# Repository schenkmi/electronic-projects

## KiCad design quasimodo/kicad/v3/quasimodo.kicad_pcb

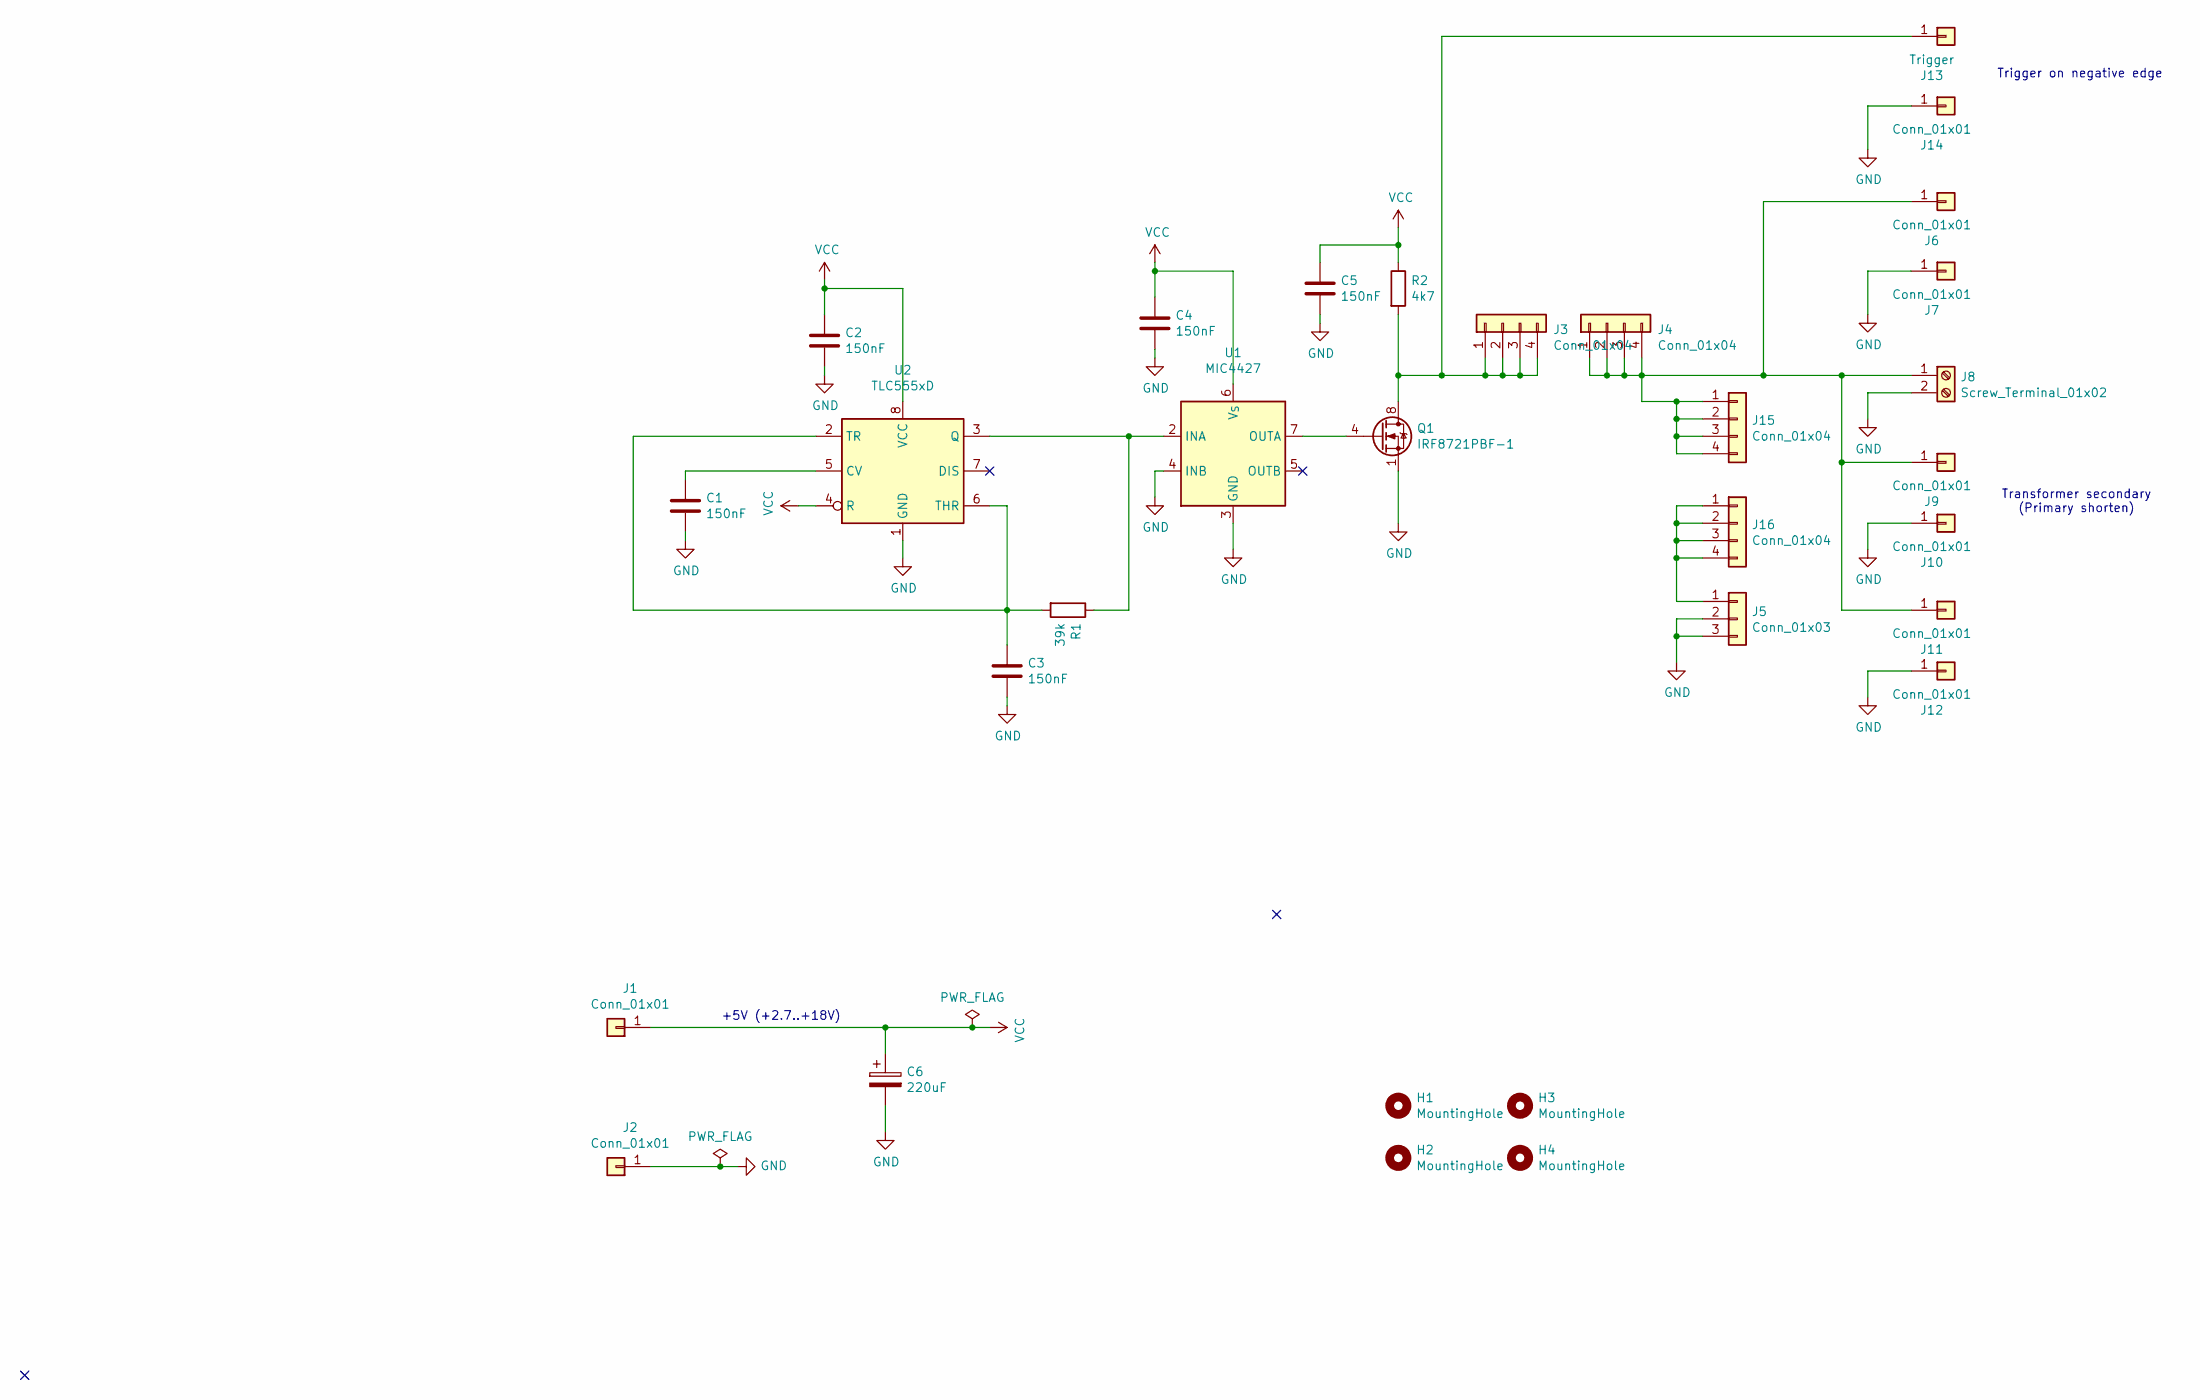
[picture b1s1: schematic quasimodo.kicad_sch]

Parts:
C1, C2, C3, C4, C5: 150nF; C_0805_2012Metric_Pad1.18x1.45mm_HandSolder
C6: 220uF; CP_Radial_D8.0mm_P3.50mm
H1, H2, H3, H4: MountingHole; MountingHole_3.2mm_M3
J1, J2, J6, J7, J9, J10, J14: Conn_01x01; Pin_D1.0mm_L10.0mm
J3, J4, J15, J16: Conn_01x04; PinSocket_1x04_P2.54mm_Vertical
J5: Conn_01x03; PinHeader_1x03_P2.54mm_Vertical
J8: Screw_Terminal_01x02; TerminalBlock_RND_205-00012_1x02_P5.00mm_Horizontal
J11, J12: Conn_01x01; Pin_D1.3mm_L11.0mm
J13: Trigger; Pin_D1.0mm_L10.0mm
Q1: IRF8721PBF-1; SOIC-8_3.9x4.9mm_P1.27mm
R1: 39k; R_0805_2012Metric_Pad1.20x1.40mm_HandSolder
R2: 4k7; R_0805_2012Metric_Pad1.20x1.40mm_HandSolder
U1: MIC4427; SOIC-8_3.9x4.9mm_P1.27mm
U2: TLC555xD; SOIC-8_3.9x4.9mm_P1.27mm

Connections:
GND: C1.2, C2.2, C3.2, C4.2, C5.2, C6.2, J2.1, J5.2, J5.3, J7.1, J8.2, J10.1, J12.1, J14.1, Q1.1 (S), Q1.2 (S), Q1.3 (S), U1.3 (GND), U1.4 (INB), U2.1 (GND)
unnamed: C1.1, U2.5 (CV)
unnamed: C3.1, R1.2, U2.2 (TR), U2.6 (THR)
unnamed: J4.1, J4.2, J4.3, J4.4, J6.1, J8.1, J9.1, J11.1, J15.1, J15.2, J15.3, J15.4
unnamed: J3.1, J3.2, J3.3, J3.4, J13.1, Q1.5 (D), Q1.6 (D), Q1.7 (D), Q1.8 (D), R2.2
unnamed: J5.1, J16.1, J16.2, J16.3, J16.4
unnamed: Q1.4 (G), U1.7 (OUTA)
unnamed: R1.1, U1.2 (INA), U2.3 (Q)
VCC: C2.1, C4.1, C5.1, C6.1, J1.1, R2.1, U1.6 (V_{S}), U2.4 (R), U2.8 (VCC)

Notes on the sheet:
+5V (+2.7..+18V)
Transformer secondary (Primary shorten)
Trigger on negative edge

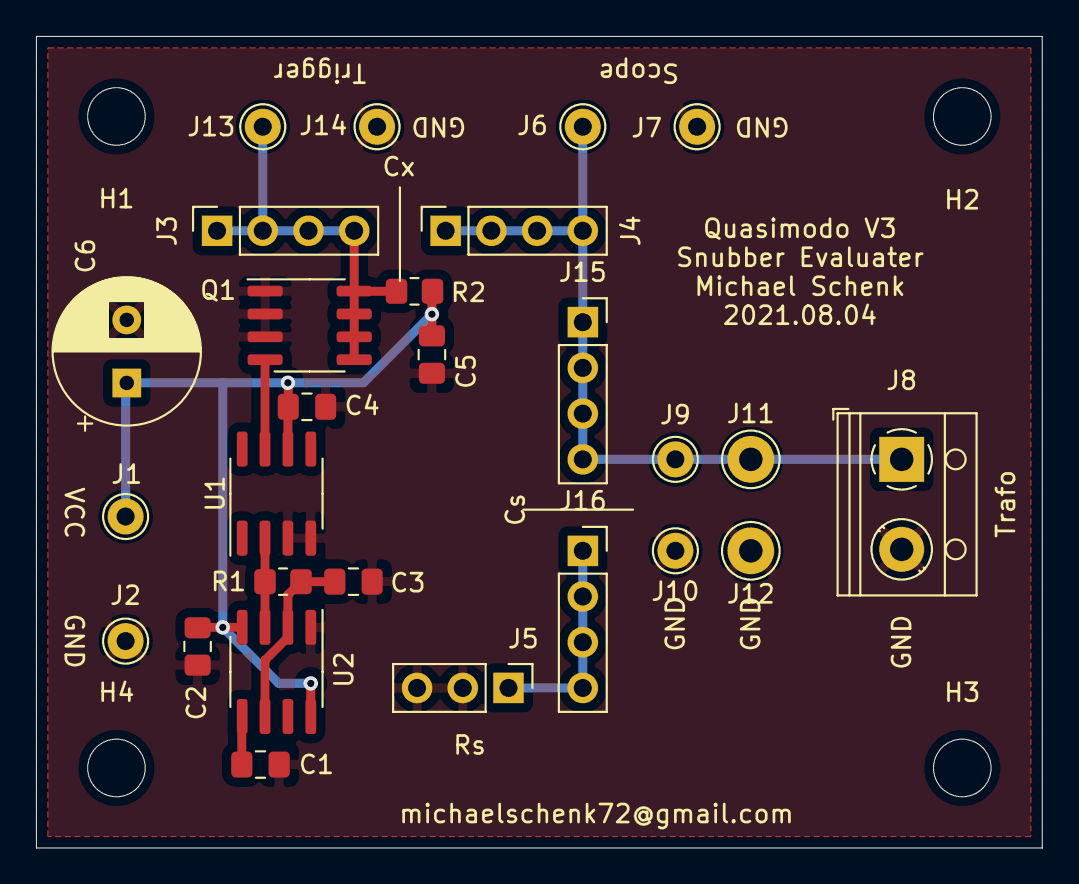
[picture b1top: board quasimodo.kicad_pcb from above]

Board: 2 copper layers, 55.9 x 45.1 mm, 31 parts (0 on the bottom side), 9 nets.

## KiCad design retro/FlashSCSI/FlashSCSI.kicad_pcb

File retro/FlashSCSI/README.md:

From: https://github.com/monotech

Intended for classic Macs starting with the Macintosh Plus, this is a Super-miniature clone of the SCSI2SD v4.2b by Michael McMaster.

Original SCSI2SD source files here: http://www.codesrc.com/gitweb/index.cgi?p=SCSI2SD.git;a=tree

If the semiconductor shortage hasn't caused them to dry up, I should have assembled stock for sale at http://monotech.fwscart.com

Mechanical parts required for assembly of the enclosure panels:
2 x screws: 2-56 UNC, 5/32" long
2 x nuts: 2-56 UNC
4 x M-F hex spacers: 3/16" body length, 5/32" screw length, 2-56 UNC thread. Example part: Fascomp FC4500-256-A

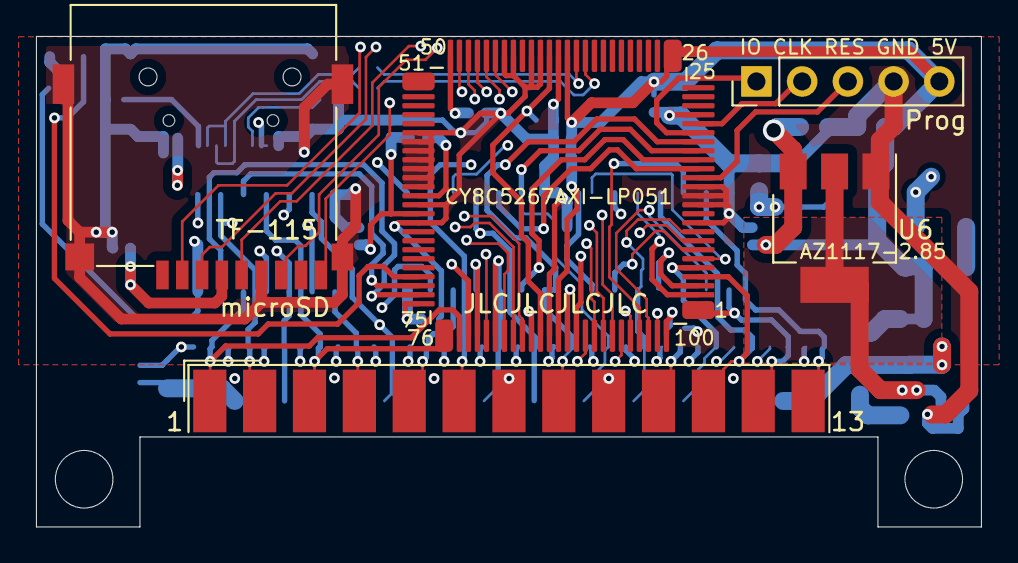
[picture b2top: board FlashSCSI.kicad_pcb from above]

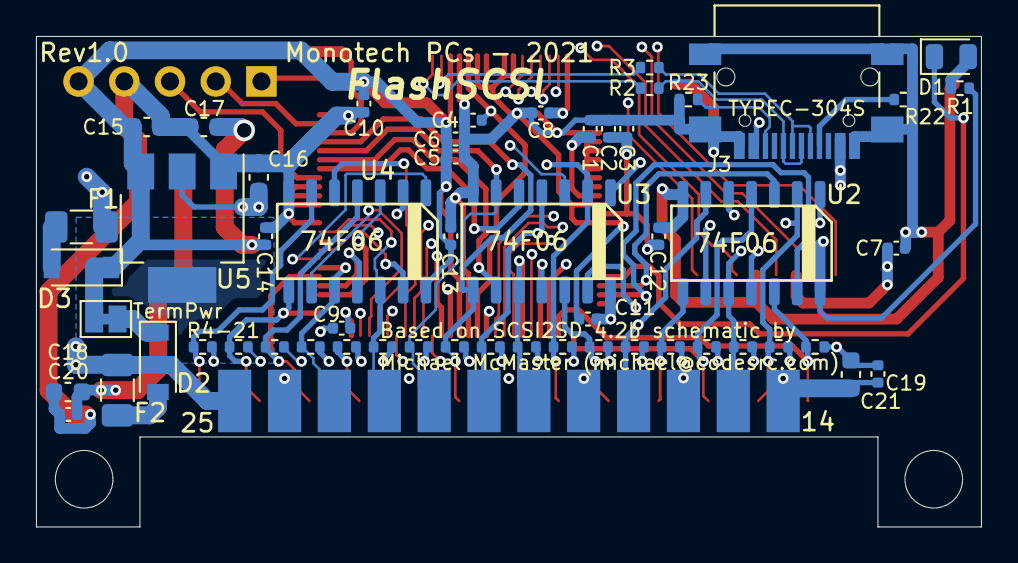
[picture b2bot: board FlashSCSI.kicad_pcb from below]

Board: 4 copper layers, 52.5 x 27.2 mm, 60 parts (55 on the bottom side), 63 nets.

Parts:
C1, C2, C4, C5: 1uF; C_0402_1005Metric
C3, C6, C7, C8, C9, C10, C11, C12, C13, C14, C19, C20: 100nF; C_0402_1005Metric
C15, C16, C17, C18, C21: 10uF; C_0603_1608Metric
D1: Activity; LED_0805_2012Metric
D2, D3: B5819W; D_SOD-123
F1, F2: 1A; Fuse_1206_3216Metric
J1: Prog; PinHeader_1x05_P2.54mm_Vertical
J2: microSD; microSD_HC_XunPu_TF-115
J3: USB; USB_C_Receptacle_XunPu_TYPEC-304S
J4: SCSI; DSUB-25_Male_EdgeMount_P2.77mm
JP1: TermPwr; SolderJumper-2_P1.3mm_Bridged_Pad1.0x1.5mm
R1: 2.2k; R_0402_1005Metric
R2, R3: 22; R_0402_1005Metric
R4, R5, R6, R7, R8, R9, R10, R11, R12, R13, R14, R15, R16, R17, R18, R19, R20, R21: 110; R_0402_1005Metric
R22, R23: 5.6k; R_0402_1005Metric
U1: CY8C5267AXI-LP051; LQFP-100_14x14mm_P0.5mm
U2, U3, U4: 74F06; SOIC-14_3.9x8.7mm_P1.27mm
U5: AZ1117-3.3; SOT-223-3_TabPin2
U6: AZ1117-2.85; SOT-223-3_TabPin2

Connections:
+3V3: C7.1, C8.1, C16.1, J2.4, U1.50, U5.2
+5V: C2.1, C3.1, C5.1, C6.1, C9.1, C10.1, C11.1, C12.1, C13.1, C14.1, C15.1, C17.1, D3.1, J1.5, JP1.2, R1.1, U1.26, U1.37, U1.65, U1.75, U1.88, U1.100, U2.14, U3.14, U4.14, U5.3, U6.3
/ACK: U1.89, U3.13
/ATN: U1.93, U2.5
/BSY: U1.90, U3.1
/CD: U1.78, U2.11
/C_USBD+: J3.A6, J3.B6, R2.2
/C_USBD-: J3.A7, J3.B7, R3.2
/DB0: U1.17, U3.9
/DB1: U1.16, U3.5
/DB2: U1.7, U4.13
/DB3: U1.6, U4.1
/DB4: U1.3, U4.11
/DB5: U1.2, U4.3
/DB6: U1.98, U4.9
/DB7: U1.97, U4.5
/DBP: U1.94, U3.3
/IO: U1.73, U2.3
/MSG: U1.82, U2.1
/REQ: U1.74, U2.13
/RST: U1.83, U2.9
/SD_MISO: J2.7, U1.45
/SD_MOSI: J2.3, U1.47
/SD_SCK: J2.5, U1.46
/SEL: U1.79, U3.11
/SWDCLK: J1.2, U1.21
/SWDIO: J1.1, U1.20
/Term_Pwr: F2.2, J4.25
/USBD+: R2.1, U1.35
/USBD-: R3.1, U1.36
/~ACK: J4.5, R19.1, U1.91, U3.12
/~ATN: J4.17, R21.1, U1.95, U2.6
/~BSY: J4.6, R20.1, U1.92, U3.2
/~CD: J4.15, R15.1, U1.80, U2.10
/~DB0: J4.8, R12.1, U1.19, U3.8
/~DB1: J4.21, R11.1, U1.18, U3.6
/~DB2: J4.22, R10.1, U1.9, U4.12
/~DB3: J4.10, R9.1, U1.8, U4.2
/~DB4: J4.23, R8.1, U1.5, U4.10
/~DB5: J4.11, R7.1, U1.4, U4.4
/~DB6: J4.12, R6.1, U1.1, U4.8
/~DB7: J4.13, R5.1, U1.99, U4.6
/~DBP: J4.20, R4.1, U1.96, U3.4
/~IO: J4.3, R13.1, U1.76, U2.4
/~MSG: J4.2, R17.1, U1.84, U2.2
/~REQ: J4.1, R14.1, U1.77, U2.12
/~RST: J4.4, R18.1, U1.85, U2.8
/~SD_CD: J2.9, U1.49
/~SD_CS: J2.2, U1.48
/~SEL: J4.19, R16.1, U1.81, U3.10
/~XRES: J1.3, U1.15
GND: C1.2, C2.2, C3.2, C4.2, C5.2, C6.2, C7.2, C8.2, C9.2, C10.2, C11.2, C12.2, C13.2, C14.2, C15.2, C16.2, C17.2, C18.2, C19.2, C20.2, C21.2, J1.4, J2.6, J2.10, J3.A1, J3.A12, J3.B1, J3.B12, J3.S1, J4.7, J4.9, J4.14, J4.16, J4.18, J4.24, R22.1, R23.1, U1.10, U1.12, U1.13, U1.14, U1.22, U1.38, U1.40, U1.41, U1.43, U1.44, U1.56, U1.57, U1.58, U1.59, U1.60, U1.61, U1.62, U1.64, U1.66, U1.87, U2.7, U3.7, U4.7, U5.1, U6.1
unnamed: C1.1, U1.63
unnamed: C4.1, U1.39, U1.86
unnamed: C18.1, C19.1, C20.1, C21.1, R4.2, R5.2, R6.2, R7.2, R8.2, R9.2, R10.2, R11.2, R12.2, R13.2, R14.2, R15.2, R16.2, R17.2, R18.2, R19.2, R20.2, R21.2, U6.2
unnamed: D1.1, U1.72
unnamed: D1.2, R1.2
unnamed: D2.1, JP1.1
unnamed: D2.2, F2.1
unnamed: D3.2, F1.1
unnamed: F1.2, J3.A4, J3.A9, J3.B4, J3.B9
unnamed: J3.A5, R22.2
unnamed: J3.B5, R23.2

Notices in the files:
retro/LittleSixteen/LittleSixteen.kicad_pcb:
Licensed under CC BY-NC-SA 4.0
